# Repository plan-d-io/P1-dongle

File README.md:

# P1-dongle
ESP32-based firmware and hardware to receive, parse, store and forward energy data coming from the P1 port of Fluvius digital meters (Flanders, Belgium). Also reads other Belgian and Dutch DSMR meters. Luxembourg meters encrypt their telegrams and are not supported.

Please see the [wiki](https://github.com/plan-d-io/P1-dongle/wiki) for extended instructions on how to build, configure and use the P1-dongle.

## Firmware and source code
I have moved all my P1 projects, this WiFi dongle as well as the LoRa transmitter and
receiver, into one code base: [plan-d-io/P1-firmware](https://github.com/plan-d-io/P1-firmware).
Since version 3.00 the dongle firmware is developed there, together with its issue
tracker and release notes. This repository keeps the hardware design and serves the
files that dongles download when they update themselves. The source code of the 2.x
firmware stays available in the history of this repository (tag `V2.23`).

## Features
- Professional looking yet easy DIY build
- Cheap (<€20 DIY cost)
- Easy to configure through a web interface or a local HTTP API
- MQTT and MQTT over TLS to your own broker
- Native integration into Home Assistant (MQTT discovery)
- Optional upload to EnergieID
- Privacy first: cloud, or even internet access entirely optional
- Automatic firmware updates (optional), with automatic rollback when a new version
  fails to start
- Source-available firmware and hardware design (PolyForm Noncommercial 1.0.0)

I do not provide any guarantees nor timelines for developing functionality. I am however available for specific functionality or developments at request. 
Contributions are welcome in [P1-firmware](https://github.com/plan-d-io/P1-firmware).

## Basic installation
1. Plug the P1-dongle into the P1 port of your digital meter
2. When the LED turns blue, connect to the `p1dongle` WiFi network
3. Open the setup page, or go to `192.168.4.1`
4. Choose your WiFi network, complete the configuration and save. Reboot the dongle to apply the new network settings; it then joins your network

# Development
- [Development roadmap](https://github.com/plan-d-io/P1-dongle/wiki/Development:-roadmap)

# Project sponsors
**Elia Innovation**

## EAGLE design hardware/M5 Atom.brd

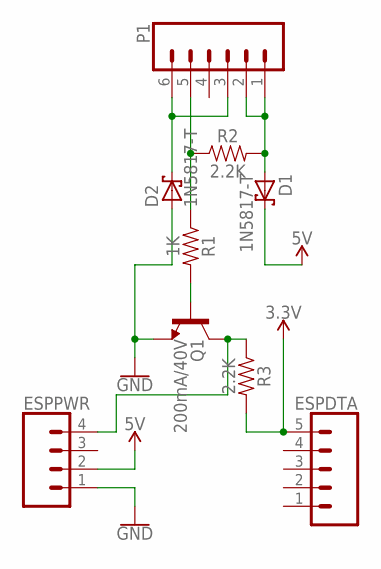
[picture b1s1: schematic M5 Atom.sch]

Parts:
D1, D2: 1N5817-T; DO41-7.6
ESPDTA: CONN_05; 1X05
ESPPWR: CONN_04PTH; 1X04
P1: CONN_06SILK_FEMALE_PTH; 1X06
Q1: 200mA/40V; TO-92
R1: 1K; AXIAL-0.3
R2, R3: 2.2K; AXIAL-0.3

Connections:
3.3V: ESPDTA.5, R3.P$2 (2)
5V: D1.C, ESPPWR.2
5VH: D1.A, P1.1, P1.2, R2.P$2 (2)
GND: D2.A, ESPPWR.1, Q1.1 (E)
GNDH: D2.C, P1.3, P1.6
unnamed: Q1.2 (B), R1.P$2 (2)
TXH: P1.5, R1.P$1 (1), R2.P$1 (1)
TXL: ESPPWR.4, Q1.3 (C), R3.P$1 (1)

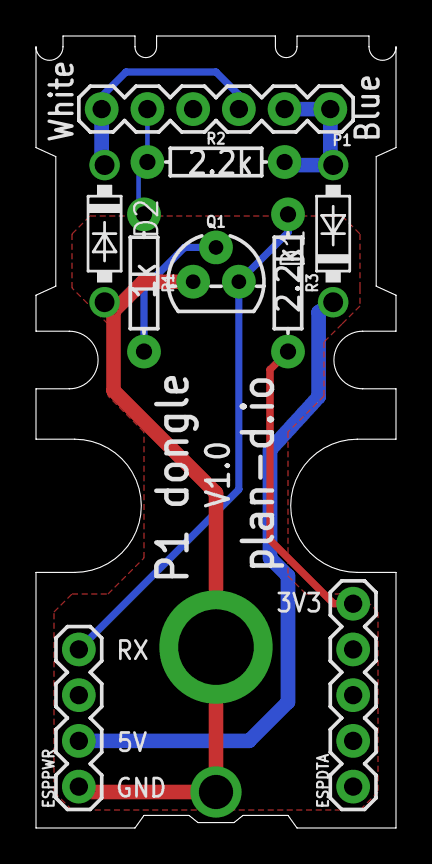
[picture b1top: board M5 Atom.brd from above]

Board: 2 copper layers, 20.0 x 44.0 mm, 9 parts (0 on the bottom side), 8 nets.

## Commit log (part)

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2022-02-23 Update files
2022-02-23 Update version
2022-03-21 Add auto-reconnect, fix sensorIds
    When in AP mode, dongle will now check if the stored SSID is back up and then reconnect. Fixes situations where, after power outage, dongle reboots before wifi router does.
2022-07-12 Fixed telegram unit parsing
2022-07-27 Upgrade to V0.91
2022-11-21 Migrate to p1connect, change topic structure, add beta fleet option
2022-11-21 add new binaries
2022-11-23 cleanup MQTT payload
2022-11-23 fix MQTT LWT for secure client
2022-11-27 Remove metrics from day/night readings
2022-12-05 Hardcoded MQTT settings
2022-12-05 Changes to GUI
    -Changed where buttons reside
    -Froze MQTT settings page
    -Updated credit line
2022-12-06 Changed sys endpoint
    Changed to plan-d/P1XXXXXX/sys/#
    Also changed throttle frequency as 60 seconds is still problematic
2022-12-12 Added Email configuration
    -Added email to WiFi screen
    -Email is saved in preferences
    -Email is sent over MQTT to sys endpoint
2022-12-12 Fix MQTT keepAlive, fix MQTT secure callback
2022-12-12 Fix indentation
2022-12-12 Fix merge conflicts
2022-12-12 Fix MQTT secure subscribe
2022-12-12 Catch empty wifi pw
2022-12-13 updated throttle data
    -Changed upload throttle to 60
    -Set KeepAlive and SocketTimeout to 2x the throttle delay to avoid disconnections a second before new data being sent
    -Reduced the upload throttle treshold to 10 instead of 15 to avoid fringe cases
    -Removed redundant setClients within the if statements
2022-12-13 Added an MQTT 'readings' endpoint
    -All changes are in splitTelegram function
    -Added a DynamicJsonDocument readings
    -Populate readings with timestamp and meter values with index '4'
    -Publish through MQTT to plan-d/P1XXXXXX/data/readings
2022-12-15 Fix timestamp issue in dsmrTelegram
2022-12-15 Version increase to 1.02
2022-12-27 Various bugfixes and improvements
2022-12-27 Fix digital meter data point fields
2022-12-27 Add average and max demand fields
2022-12-27 Limit MQTT uploads to selected telegram values
2022-12-27 Round mqtt values to 3 decimals max
2022-12-27 Add limited JSON string for webAPI
2022-12-28 Add webAPI
2022-12-28 Add avg and max demand to webmin
2022-12-28 Fix MQTT payload
2022-12-28 Add object_id to MQTT payload for more stable Home Assistant MQTT discovery
2022-12-28 Change hostname to p1dongle, improve mDNS
2022-12-28 Move temporary bootstrap code
2022-12-28 Improve MQTT user feedback flow
2022-12-28 Make syslog available through webmin
2022-12-28 Fix syslog webmin interface
2022-12-28 Improve HA MQTT discovery, remove entities from HA before reboot
2022-12-28 Increase version to 1.02
2022-12-28 Add 1.02 binaries
2022-12-28 Increase version
2022-12-28 Fix totGasCon in webmin
2022-12-28 Add legacy binaries
2022-12-29 Fix bootstrap
2023-02-18 Update binaries
2023-03-12 Fix flash formatting/nvs loss issues
2023-03-12 Fix file updater
2023-03-12 Fix wifi scan
2023-04-04 Increase version to 103
2023-04-11 Improve NVS and flash stability
2023-04-11 Add SPIFFS remote restore
2023-04-11 Change restore file order
2023-04-11 Cleanup
2023-04-11 Move aggregate readings
2023-04-11 Move jsonreadings
2023-04-11 Fix mqtt reconnect
2023-04-12 Bring up to date with upstream
2023-04-12 Add remote restore
2023-04-12 Create restore
2023-04-12 Add captar fields
2023-04-12 Re-add cert bundle
2023-04-13 Revert version for testing
2023-04-13 Add alpha branch option
2023-04-13 Add release channel debug info
2023-04-13 Test upgrade
2023-04-13 Fix restore/upgrade
2023-04-13 Rebase to develop
2023-04-14 Fix restore
2023-04-14 Try to fix upgrade
2023-04-14 Add temp to fix upgrade
2023-04-28 Add SPIFFS format fix
2023-07-04 Add binaries for older dongles
2023-07-07 First merge of refactored/legacy code
2023-07-07 Refactoring
2023-07-10 SPIFFS check
2023-07-11 Extended refactoring
2023-07-12 Add mqtt checks
2023-07-27 SPIFFS fix, LED behaviour
2023-07-28 Revert apssid name
2023-07-28 Revert version
2023-07-29 Fix upload throttle
2023-10-12 Push to V2.0
2023-10-14 Add real-time data in webmin
2023-10-14 Refactor payload formatting
2023-10-15 Update webmin
2023-10-18 Update config
2023-10-24 Cache config string
2023-10-27 Add new EID integration
2023-10-28 Add static IP option
2023-10-28 Enhance EID integration
2023-11-02 Migrate SPIFFS to LittleFS
2023-11-02 Remove static HTML file restore
2023-11-03 Improve EID integration
2023-11-04 Re-add Home Assistant integration
2023-11-04 Fix upgrade url
2023-11-04 Set default upload interval
2023-11-20 Add payload format to webmin
2023-11-20 Upgrade to V2.x
2023-11-20 Move cert bundle
2023-11-20 Move EID claim code to UUID
2023-11-20 Revert binaries
2023-11-21 Clean up config
2023-11-21 Fix EID UUID generation
2023-11-21 Update to main
2023-11-22 Make telegram values selectable
2023-11-22 Limit config json length
2023-11-23 Make telegram readings selectable
2023-11-23 Clean up configuration
2023-11-23 Clean up serial debug
2023-11-23 Add smart reboot for connection issues
2023-11-28 Remove bootstraps
2023-12-03 Fix factory reset by manually deleting config entries
2023-12-03 Fix telegram request line not asserted by default
2023-12-03 Add reboot reseaon when rebooting from webmin
2023-12-04 Add partitions file
2023-12-05 Add TLS restore option to webmin
2023-12-05 Add EID UUID renew option to webmin
2023-12-05 Separate UUID & claim code
2023-12-13 Change EID deviceName and claimCode
2023-12-13 Clean up init
2023-12-13 Fix EID daily interval setting
2023-12-13 Fix config reset
2023-12-17 Try fix EID gas/water/heat uploads
2023-12-19 Prepare TLS switch
2023-12-21 New TLS fix
2023-12-22 Trim TLS bundle
2023-12-23 Fix DSMR timestamp
2023-12-23 Fix EID integration
2023-12-23 Update TLS bundle
2023-12-24 Improve HA MQTT autodiscovery
2023-12-24 Add filter for spurious meter readings
2024-01-03 Close and clean up SSL socket after uploading to EID
2024-01-10 Improve spurious reading detection
2024-01-10 Continously scan for Mbus meters
2024-01-18 Mark reading as invalid when spurious value detected
2024-01-18 Update versin
2024-01-18 Fix reboot over MQTT
2024-01-22 Further refine spurrious reading check
2024-01-26 Further refine spurious reading detection
2024-04-01 Fix negative values (injection) being discarded as spurious reading
2024-04-01 Fix MQTT reboot

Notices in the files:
parts and their libraries:
SparkFun-Connectors: Licensing: Creative Commons ShareAlike 4.0 International - https://creativecommons.org/licenses/by-sa/4.0
